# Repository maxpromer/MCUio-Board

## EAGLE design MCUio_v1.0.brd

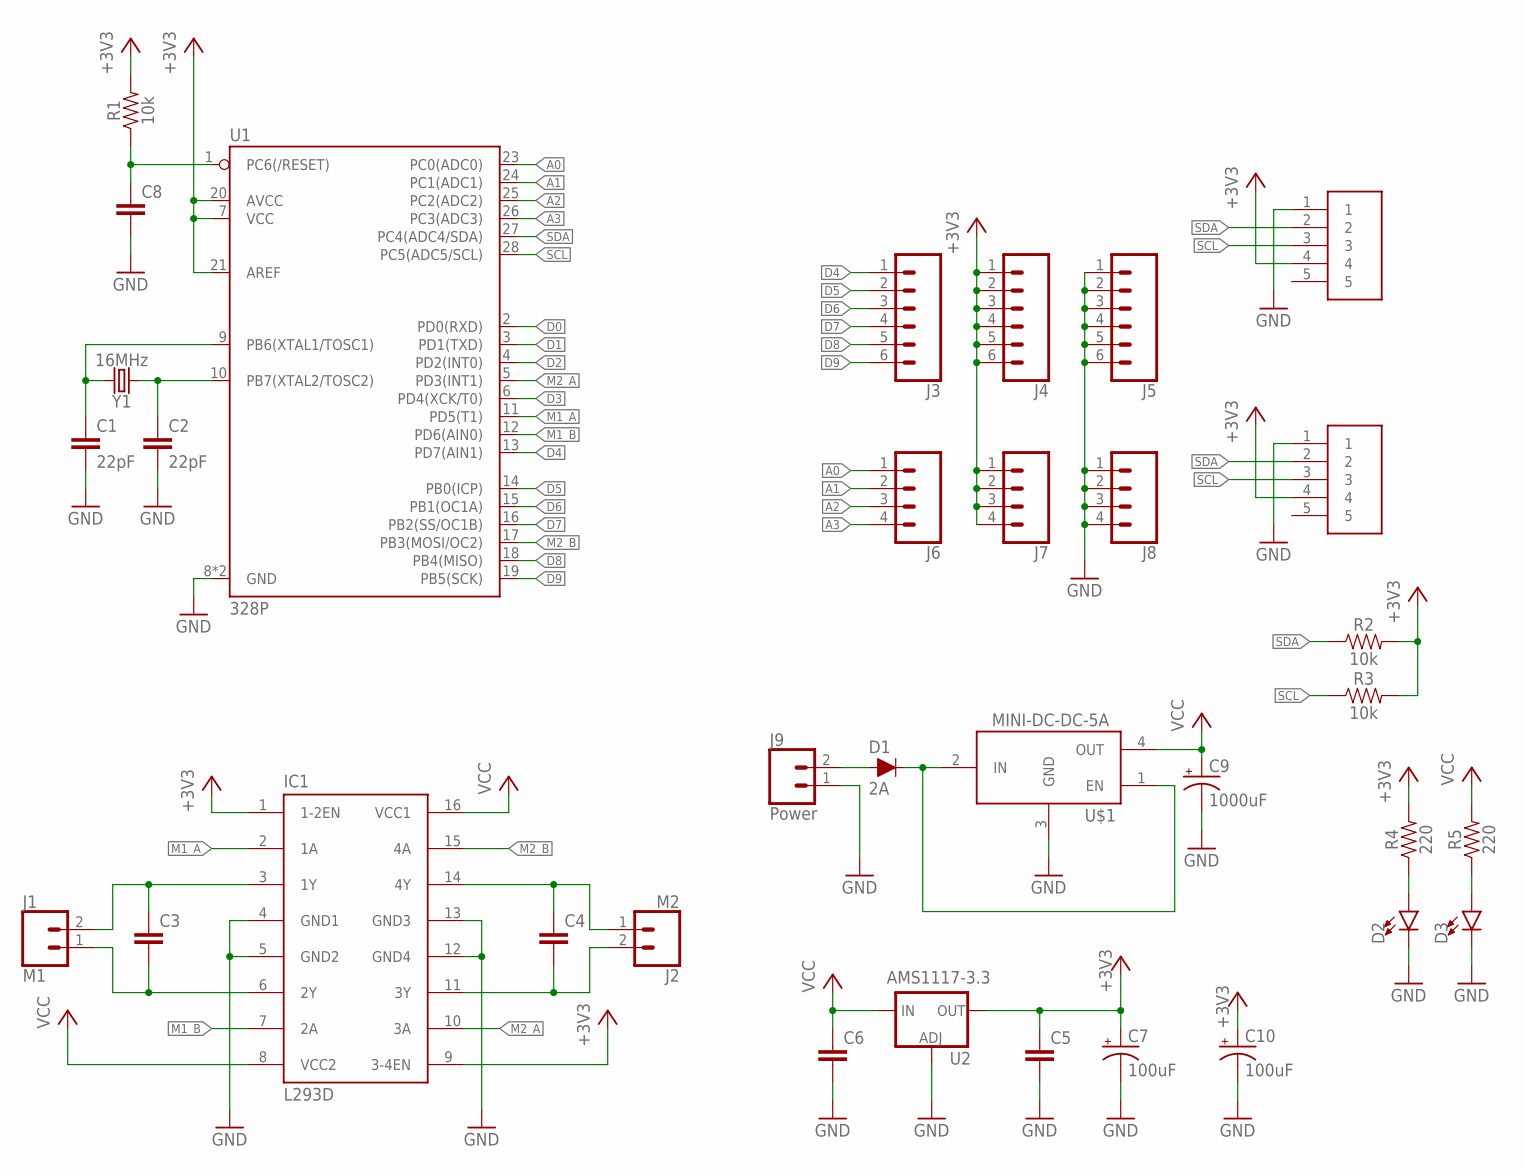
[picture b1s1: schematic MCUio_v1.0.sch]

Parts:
C1, C2: 22pF; CAP-PTH-2.54
C3, C4, C5, C6, C8: 0.1uF; C5B2.5
C7, C10: 100uF; CPOL-RADIAL-2.5MM-6.5MM
C9: 1000uF; CPOL-RADIAL-5MM-10MM
D1: 2A; DIODE-1N4001-KIT
D2, D3: LED3MM; LED_3MM
IC1: L293D; DIL16
J1: M1; SCREWTERMINAL-5MM-2
J2: M2; SCREWTERMINAL-5MM-2
J3, J4, J5: CONN_06SILK_FEMALE_PTH; 1X06
J6, J7, J8: CONN_04PTH; 1X04
J9: Power; SCREWTERMINAL-5MM-2
R1, R2, R3: 10k; AXIAL-0.3
R4, R5: 220; 0603
U1: 328P; DIP28
U2: AMS1117-3.3; SOT223
U$1: MINI-DC-DC-5A; MINI-DC-DC-3A
U$2, U$3: JST5PIN
Y1: 16MHz; HC49US

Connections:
+3V3: C5.1, C7.1 (+), C10.1 (+), IC1.1 (1-2EN), IC1.9 (3-4EN), J4.1, J4.2, J4.3, J4.4, J4.5, J4.6, J7.1, J7.2, J7.3, J7.4, R1.P$2 (2), R2.P$2 (2), R3.P$2 (2), R4.2, U1.7 (VCC), U1.20 (AVCC), U1.21 (AREF), U2.2 (OUT), U2.4 (OUT), U$2.4, U$3.4
A0: J6.1, U1.23 (PC0(ADC0))
A1: J6.2, U1.24 (PC1(ADC1))
A2: J6.3, U1.25 (PC2(ADC2))
A3: J6.4, U1.26 (PC3(ADC3))
D0: U1.2 (PD0(RXD))
D1: U1.3 (PD1(TXD))
D2: U1.4 (PD2(INT0))
D3: U1.6 (PD4(XCK/T0))
D4: J3.1, U1.13 (PD7(AIN1))
D5: J3.2, U1.14 (PB0(ICP))
D6: J3.3, U1.15 (PB1(OC1A))
D7: J3.4, U1.16 (PB2(SS/OC1B))
D8: J3.5, U1.18 (PB4(MISO))
D9: J3.6, U1.19 (PB5(SCK))
GND: C1.2, C2.2, C5.2, C6.2, C7.2 (-), C8.2, C9.-, C10.2 (-), D2.K (C), D3.K (C), IC1.4 (GND1), IC1.5 (GND2), IC1.12 (GND4), IC1.13 (GND3), J5.1, J5.2, J5.3, J5.4, J5.5, J5.6, J8.1, J8.2, J8.3, J8.4, J9.1, U1.8 (GND), U1.22 (GND), U2.1 (ADJ), U$1.3 (GND), U$2.1, U$3.1
M1_A: IC1.2 (1A), U1.11 (PD5(T1))
M1_B: IC1.7 (2A), U1.12 (PD6(AIN0))
M2_A: IC1.10 (3A), U1.5 (PD3(INT1))
M2_B: IC1.15 (4A), U1.17 (PB3(MOSI/OC2))
unnamed: C1.1, U1.9 (PB6(XTAL1/TOSC1)), Y1.2
unnamed: C2.1, U1.10 (PB7(XTAL2/TOSC2)), Y1.1
unnamed: C8.1, R1.P$1 (1), U1.1 (PC6(/RESET))
unnamed: D1.A, J9.2
unnamed: D1.C, U$1.1 (EN), U$1.2 (IN)
unnamed: D2.A, R4.1
unnamed: D3.A, R5.1
unnamed: C3.1, IC1.3 (1Y), J1.2
unnamed: C3.2, IC1.6 (2Y), J1.1
unnamed: C4.1, IC1.14 (4Y), J2.1
unnamed: C4.2, IC1.11 (3Y), J2.2
SCL: R3.P$1 (1), U1.28 (PC5(ADC5/SCL)), U$2.3, U$3.3
SDA: R2.P$1 (1), U1.27 (PC4(ADC4/SDA)), U$2.2, U$3.2
VCC: C6.1, C9.+, IC1.8 (VCC2), IC1.16 (VCC1), R5.2, U2.3 (IN), U$1.4 (OUT)

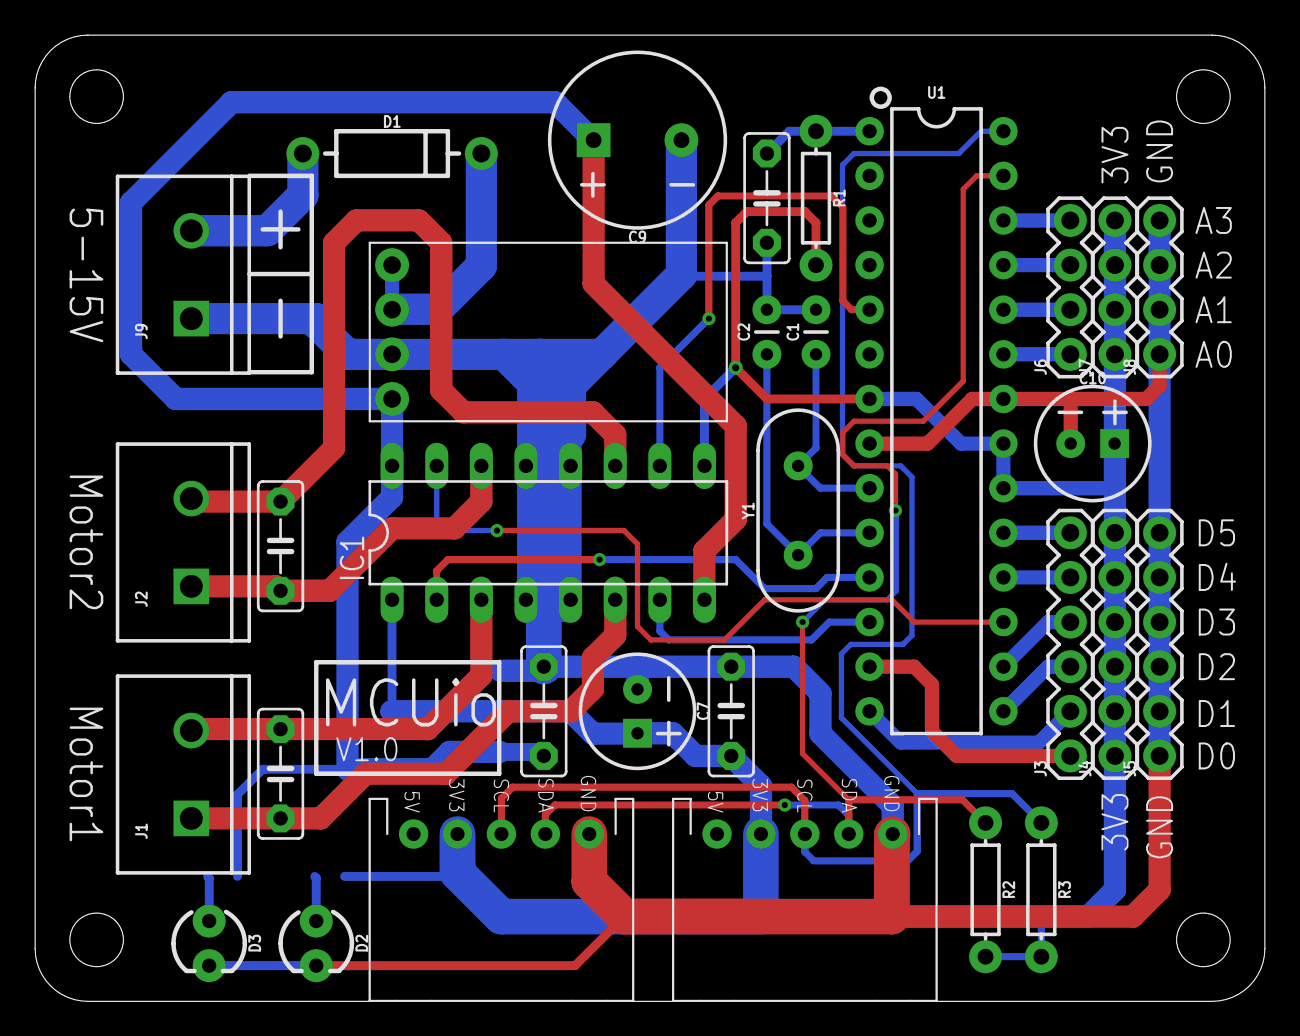
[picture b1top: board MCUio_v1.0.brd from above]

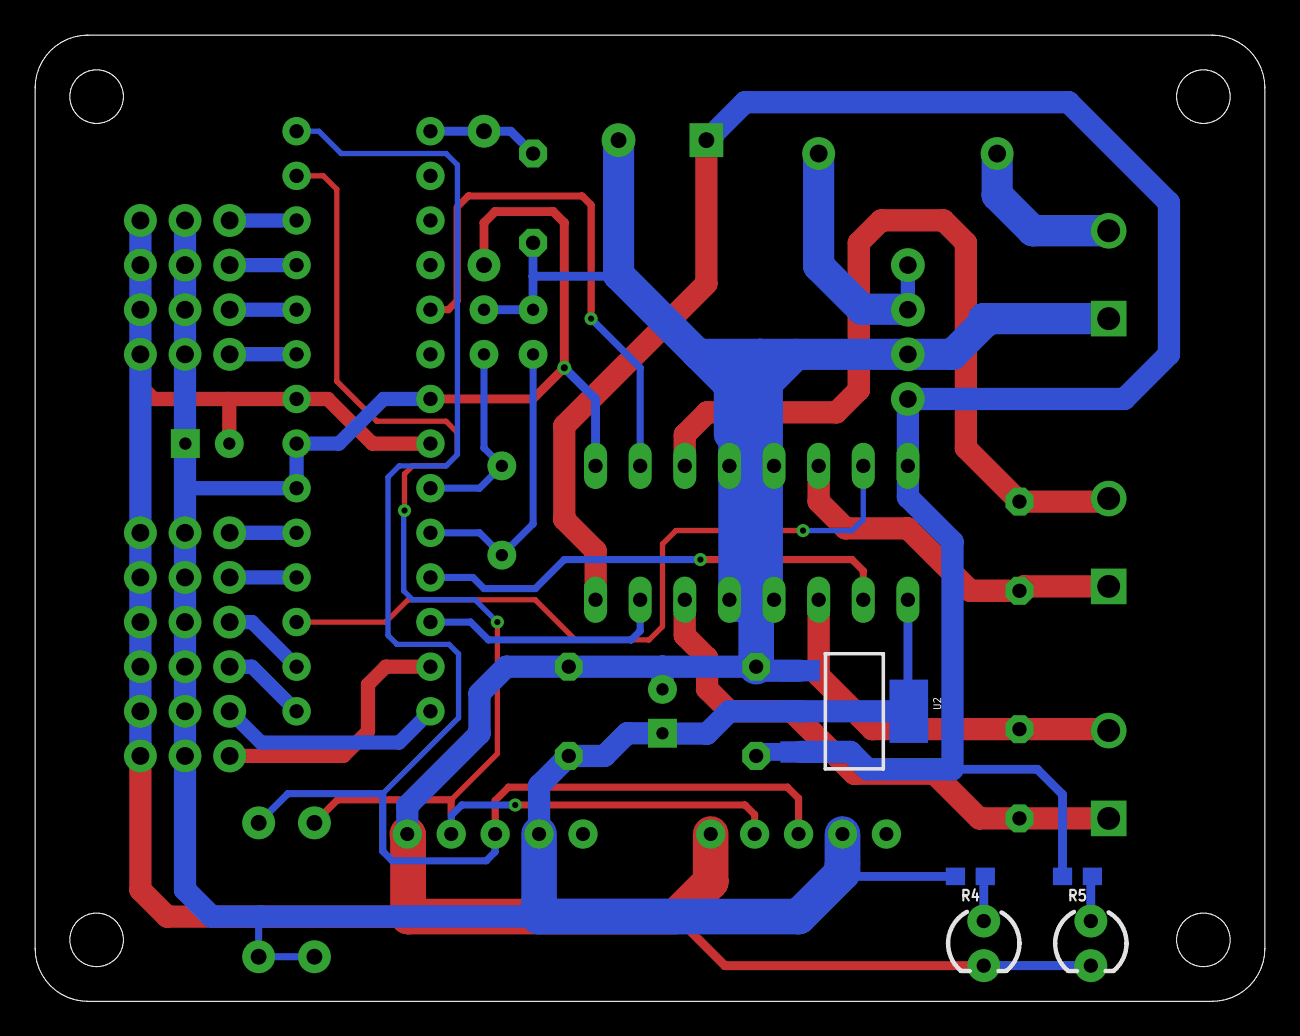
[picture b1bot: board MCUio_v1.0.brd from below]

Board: 2 copper layers, 70.0 x 55.0 mm, 34 parts (3 on the bottom side), 30 nets.

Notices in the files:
parts and their libraries:
SparkFun-Capacitors: Licensing: Creative Commons ShareAlike 4.0 International - https://creativecommons.org/licenses/by-sa/4.0
